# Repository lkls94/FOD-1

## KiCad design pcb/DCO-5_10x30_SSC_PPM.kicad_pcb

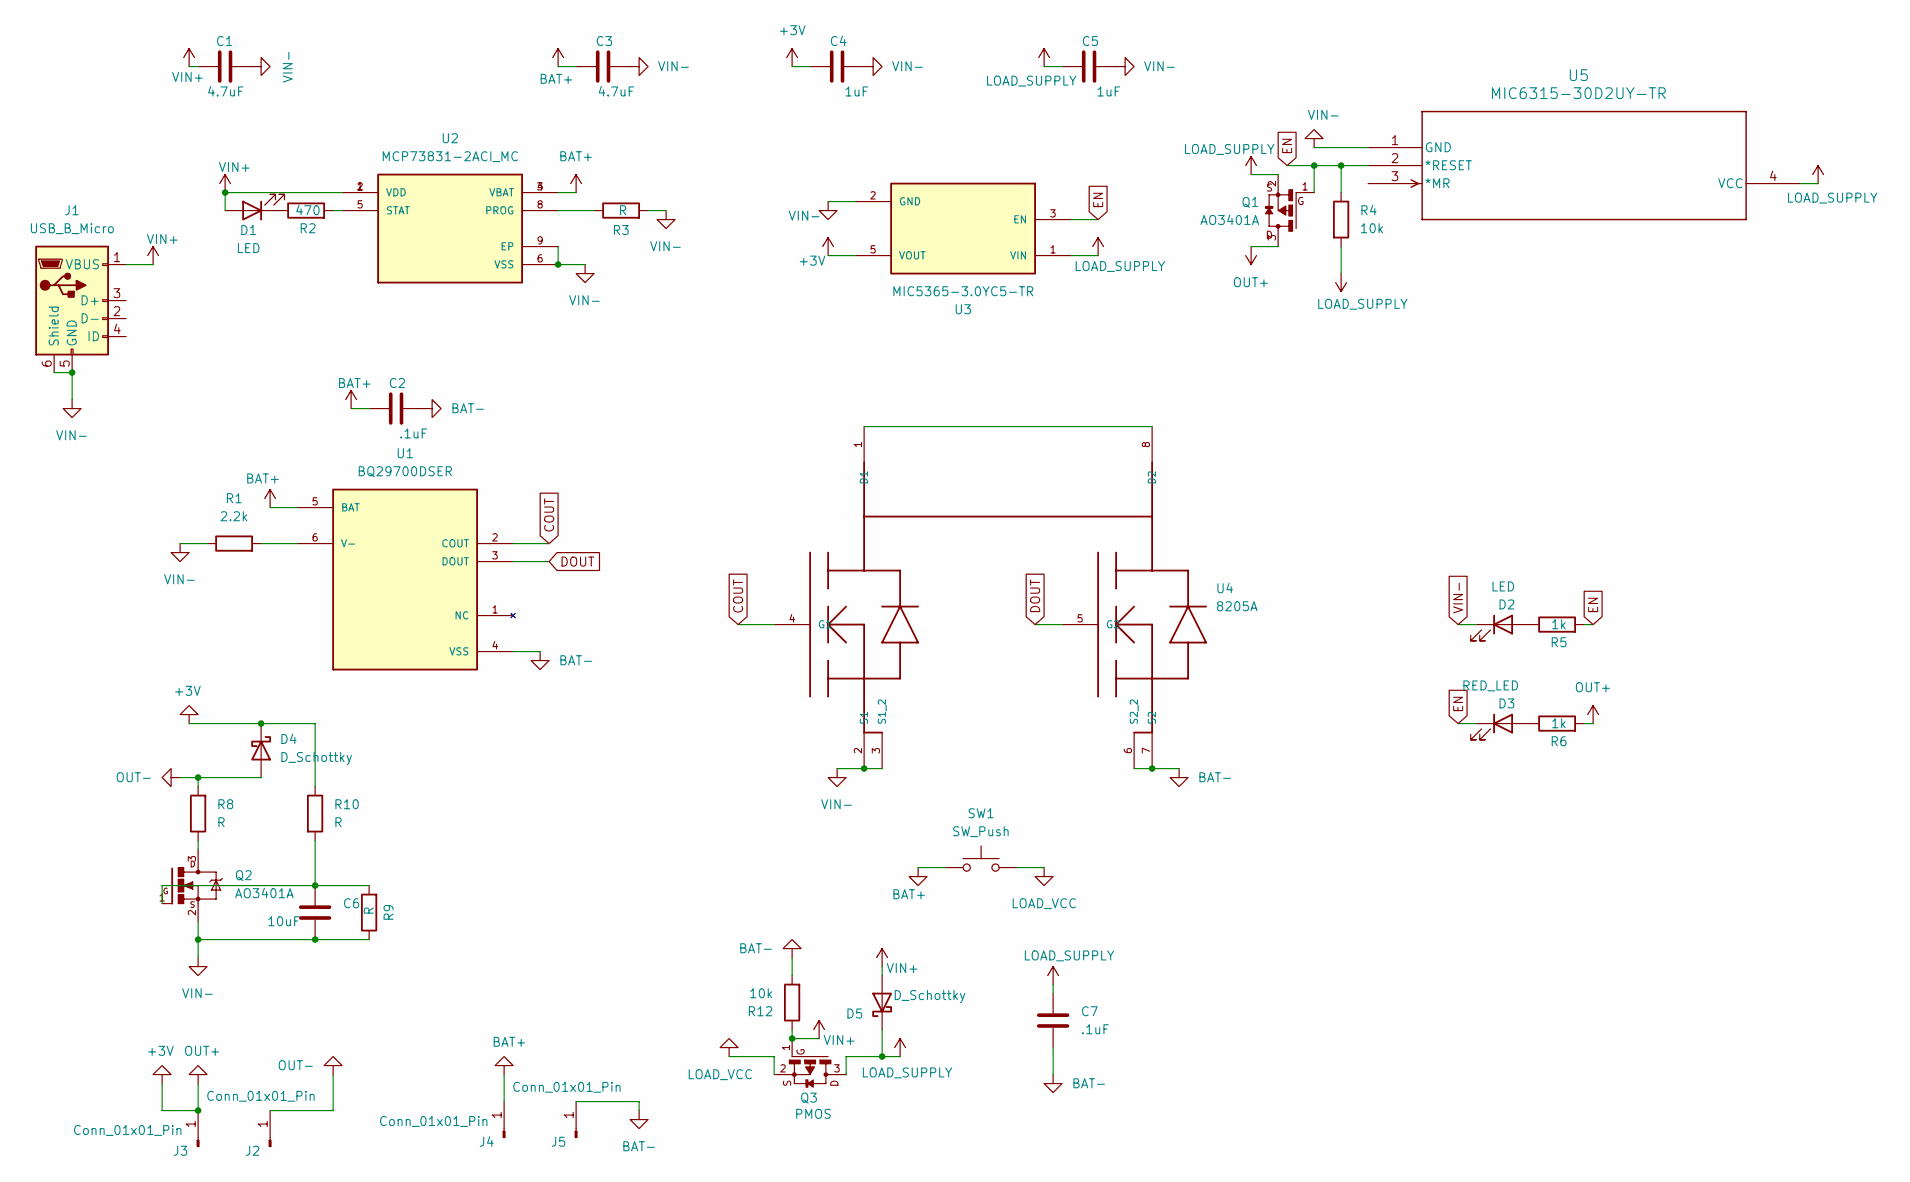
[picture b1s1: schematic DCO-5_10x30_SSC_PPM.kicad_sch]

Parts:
C1, C3: 4.7uF; C_0402_1005Metric_Pad0.74x0.62mm_HandSolder
C2, C7: .1uF; C_0402_1005Metric_Pad0.74x0.62mm_HandSolder
C4, C5: 1uF; C_0402_1005Metric_Pad0.74x0.62mm_HandSolder
C6: 10uF; C_0603_1608Metric
D1, D2: LED; LED_0402_1005Metric_Pad0.77x0.64mm_HandSolder
D3: RED_LED; LED_0402_1005Metric_Pad0.77x0.64mm_HandSolder
D4, D5: D_Schottky; D_SMA
J1: USB_B_Micro; USB-Micro-B_U-D-M7DS-G-1
J2, J3, J4, J5: Conn_01x01_Pin; PinHeader_1x01_P1.27mm_Vertical
Q1: AO3401A; SOT23
Q2: AO3401A; SOT23; PARTREV 30 Jan 2018
Q3: PMOS; SOT23
R1: 2.2k; R_0402_1005Metric_Pad0.72x0.64mm_HandSolder
R2: 470; R_0402_1005Metric_Pad0.72x0.64mm_HandSolder
R3, R9: R; R_0402_1005Metric_Pad0.72x0.64mm_HandSolder
R4: 10k; R_0402_1005Metric_Pad0.72x0.64mm_HandSolder
R5, R6: 1k; R_0402_1005Metric_Pad0.72x0.64mm_HandSolder
R8, R10: R; R_0402_1005Metric
R12: 10k; R_0402_1005Metric
SW1: SW_Push; PinHeader_1x02_P1.27mm_Vertical
U1: BQ29700DSER; SON50P150X150X80-6N; PARTREV G
U2: MCP73831-2ACI_MC; SON50P200X300X100-9N; PARTREV G
U3: MIC5365-3.0YC5-TR; SOT65P210X110-5N; PARTREV 3.1 - July 16, 2013
U4: 8205A; TSSOP8
U5: MIC6315-30D2UY-TR; SOT-143_M4_MCH

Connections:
+3V: C4.2, D4.1 (K), J3.1, Q1.3, R6.2, R10.1, U3.5 (VOUT)
BAT+: C2.2, C3.2, J4.1, SW1.1, U1.5 (BAT), U2.3 (VBAT), U2.4 (VBAT)
BAT-: C2.1, C7.2, J5.1, R12.2, U1.4 (VSS), U4.6 (S2_2), U4.7 (S2)
COUT: U1.2 (COUT), U4.4 (G1)
DOUT: U1.3 (DOUT), U4.5 (G2)
EN: D3.1 (K), Q1.1, R4.1, R5.2, U3.3 (EN), U5.2 (*RESET)
LOAD_SUPPLY: C5.2, C7.1, D5.1 (K), Q1.2, Q3.3, R4.2, U3.1 (VIN), U5.4 (VCC)
LOAD_VCC: Q3.2, SW1.2
unnamed: C6.1, Q2.1, R9.2, R10.2
unnamed: D1.1 (K), R2.1
unnamed: D2.2 (A), R5.1
unnamed: D3.2 (A), R6.1
unnamed: Q2.3, R8.1
unnamed: R1.2, U1.6 (V-)
unnamed: R3.1, U2.8 (PROG)
unnamed: R2.2, U2.5 (STAT)
unnamed: U4.1 (D1), U4.8 (D2)
OUT-: D4.2 (A), J2.1, R8.2
VIN+: C1.2, D1.2 (A), D5.2 (A), J1.1 (VBUS), Q3.1, R12.1, U2.1 (VDD), U2.2 (VDD)
VIN-: C1.1, C3.1, C4.1, C5.1, C6.2, D2.1 (K), J1.5 (GND), J1.6 (Shield), Q2.2, R1.1, R3.2, R9.1, U2.6 (VSS), U2.9 (EP), U3.2 (GND), U4.2 (S1), U4.3 (S1_2), U5.1 (GND)

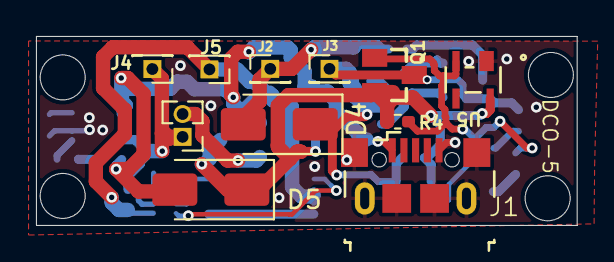
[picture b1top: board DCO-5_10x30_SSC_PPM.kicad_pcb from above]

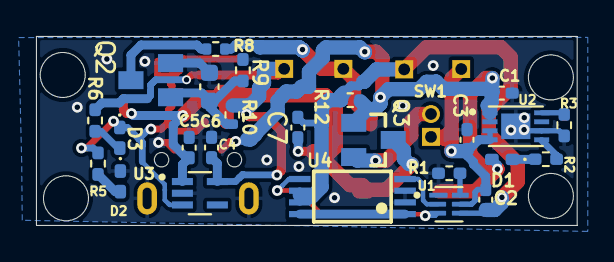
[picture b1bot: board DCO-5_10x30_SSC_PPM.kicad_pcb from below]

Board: 2 copper layers, 30.0 x 10.5 mm, 36 parts (25 on the bottom side), 20 nets.

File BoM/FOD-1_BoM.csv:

Id,Designator,Footprint,Quantity,Designation,P/DNP
1,Q2,SOT23,1,IRLML6344TRPBF,P
2,"D5,D4",D_SMA,2,D_Schottky,P
3,SW1,PinHeader_1x02_P1.27mm_Vertical,1,SW_Push,DNP
4,",,,",,4,,P
5,U5,SOT-143_M4_MCH,1,MIC6315-30D2UY-TR,P
6,"J2,J5,J3,J4",PinHeader_1x01_P1.27mm_Vertical,4,Conn_01x01_Pin,DNP
7,J1,USB-Micro-B_U-D-M7DS-G-1,1,USB_B_Micro,P
8,R9,R_0402_1005Metric_Pad0.72x0.64mm_HandSolder,4,47k,P
9,Q1,SOT23,1,AO3401A,P
10,U4,TSSOP8,1,8205A,P
11,"C1,C3",C_0402_1005Metric_Pad0.74x0.62mm_HandSolder,2,4.7uF,P
12,"D1,D2",LED_0402_1005Metric_Pad0.77x0.64mm_HandSolder,2,LED,P
13,C2,C_0402_1005Metric_Pad0.74x0.62mm_HandSolder,1,.1uF,P
14,R2,R_0402_1005Metric_Pad0.72x0.64mm_HandSolder,1,470,P
15,R12,R_0402_1005Metric,1,10k,P
16,U3,SOT65P210X110-5N,1,MIC5365-3.0YC5-TR,P
17,"C4,C5",C_0402_1005Metric_Pad0.74x0.62mm_HandSolder,2,1uF,P
18,C7,C_0603_1608Metric_Pad1.08x0.95mm_HandSolder,1,.1uF,P
19,U1,SON50P150X150X80-6N,1,BQ29700DSER,P
20,C6,C_0603_1608Metric,1,10uF,P
21,R8,R_0402_1005Metric,2,20E,P
22,U2,SON50P200X300X100-9N,1,MCP73831-2ACI_MC,P
23,Q3,SOT23,1,AO3401A,P
24,D3,LED_0402_1005Metric_Pad0.77x0.64mm_HandSolder,1,RED_LED,P
25,"R6,R5",R_0402_1005Metric_Pad0.72x0.64mm_HandSolder,2,1k,P
26,R1,R_0402_1005Metric_Pad0.72x0.64mm_HandSolder,1,2.2k,P
27,"R4,R3,R10",R_0402_1005Metric_Pad0.72x0.64mm_HandSolder,2,10k,P

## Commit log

2025-06-24 Hardware files
